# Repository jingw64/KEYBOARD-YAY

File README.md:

# J&R's Keyboard Project

## Overview

For this project, we wish to learn the process of making a keyboard. Due to how well documented and relatively simple keyboards are, we decided that creating one from the ground up will be a good first project for developing important skills.

After the completion of this project, we will:

- Understand the basics of navigating git and github
- Know the process of designing a PCB
- Develop collaboration skills
- Gain experience in writing software for an embedded system

## Projects Thus Far

- [~~Macropad~~ Burgerpad](./macropads/burgerpad/)
  - Our very first project in the keyboard series to get us familiar with software and the PCB designing process
  - A macropad in a layout that looks similar to a burger; made to print out Greek letters to make writing equations and lab reports easier

## Tools

### Softwares

- KiCad
  - For schematic and PCB design
- VSCode
  - For managing files on github and writing firmware
- Notion
  - For writing up documentation that require collaborative work
  
### Libraries

- [Marbastlib](https://github.com/ebastler/marbastlib?ref=ohmbedded.com)
  - A KiCad library specifically for designing keyboard PCBs

## References

### General Process

- [How to Build a Custom Keyboard From Scratch | Part 1 Layout and Design](https://www.youtube.com/watch?v=IJxuzyO9b8M) - Casual Coders
- [Custom Keyboard From Scratch Part 2](https://www.youtube.com/watch?v=fYNxG8RwpaE) - Casual Coders
- [How to Design Mechanical Keyboard PCBs with Kicad](https://www.youtube.com/watch?v=8WXpGTIbxlQ) - Joe Scotto

### Functionality

- [How a Mechanical Keyboard Works (Matrix and Direct Wiring)](https://www.youtube.com/watch?v=7LyziNdFlew) - Joe Scotto

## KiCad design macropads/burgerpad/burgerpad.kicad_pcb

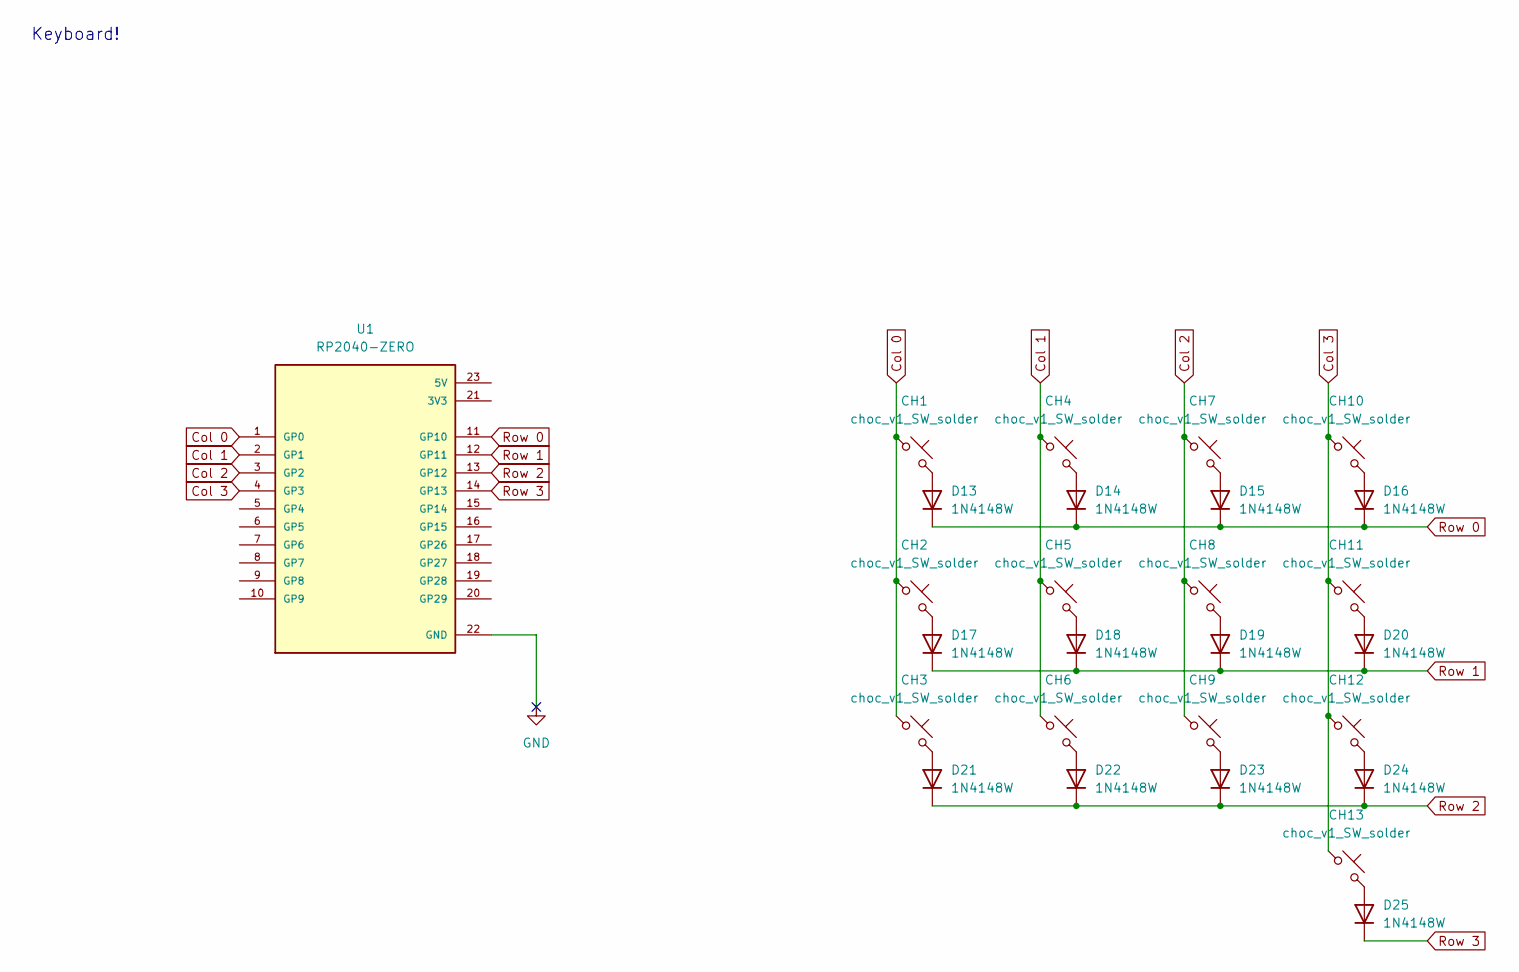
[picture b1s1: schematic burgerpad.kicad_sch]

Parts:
CH1, CH2, CH3, CH4, CH5, CH6, CH7, CH8, CH9, CH10, CH11, CH12, CH13: choc_v1_SW_solder; SW_choc_v1_1u
D13, D14, D15, D16, D17, D18, D19, D20, D21, D22, D23, D24, D25: 1N4148W; D_SOD-123
U1: RP2040-ZERO; MODULE_RP2040-ZERO; PARTREV NA

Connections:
Col 0: CH1.1, CH2.1, CH3.1, U1.1 (GP0)
Col 1: CH4.1, CH5.1, CH6.1, U1.2 (GP1)
Col 2: CH7.1, CH8.1, CH9.1, U1.3 (GP2)
Col 3: CH10.1, CH11.1, CH12.1, CH13.1, U1.4 (GP3)
GND: U1.22 (GND)
unnamed: CH1.2, D13.2 (A)
unnamed: CH4.2, D14.2 (A)
unnamed: CH7.2, D15.2 (A)
unnamed: CH10.2, D16.2 (A)
unnamed: CH2.2, D17.2 (A)
unnamed: CH5.2, D18.2 (A)
unnamed: CH8.2, D19.2 (A)
unnamed: CH11.2, D20.2 (A)
unnamed: CH3.2, D21.2 (A)
unnamed: CH6.2, D22.2 (A)
unnamed: CH9.2, D23.2 (A)
unnamed: CH12.2, D24.2 (A)
unnamed: CH13.2, D25.2 (A)
Row 0: D13.1 (K), D14.1 (K), D15.1 (K), D16.1 (K), U1.11 (GP10)
Row 1: D17.1 (K), D18.1 (K), D19.1 (K), D20.1 (K), U1.12 (GP11)
Row 2: D21.1 (K), D22.1 (K), D23.1 (K), D24.1 (K), U1.13 (GP12)
Row 3: D25.1 (K), U1.14 (GP13)

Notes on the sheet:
Keyboard!

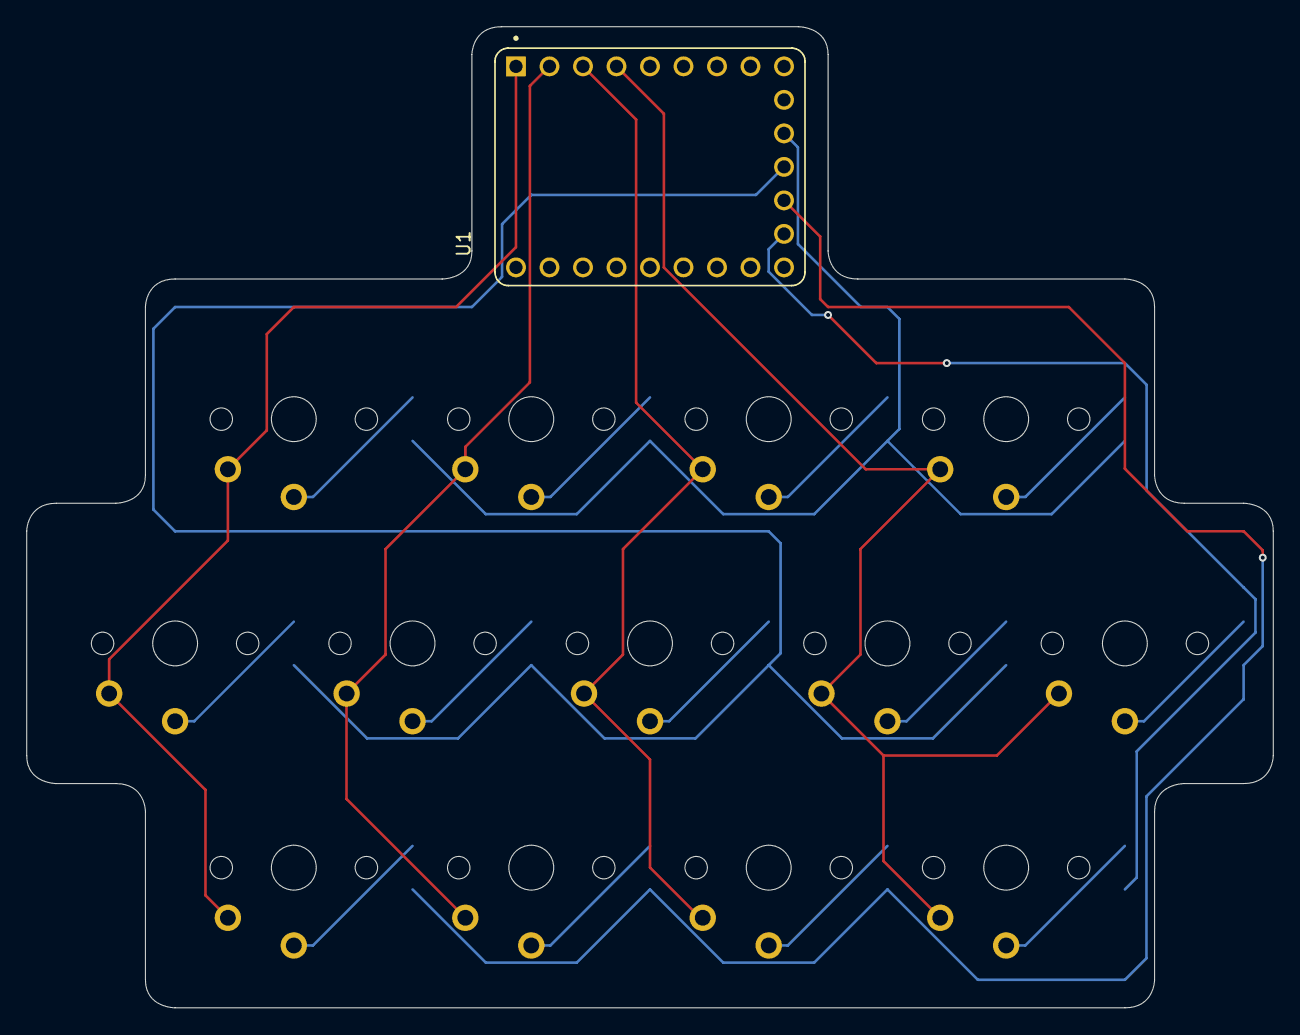
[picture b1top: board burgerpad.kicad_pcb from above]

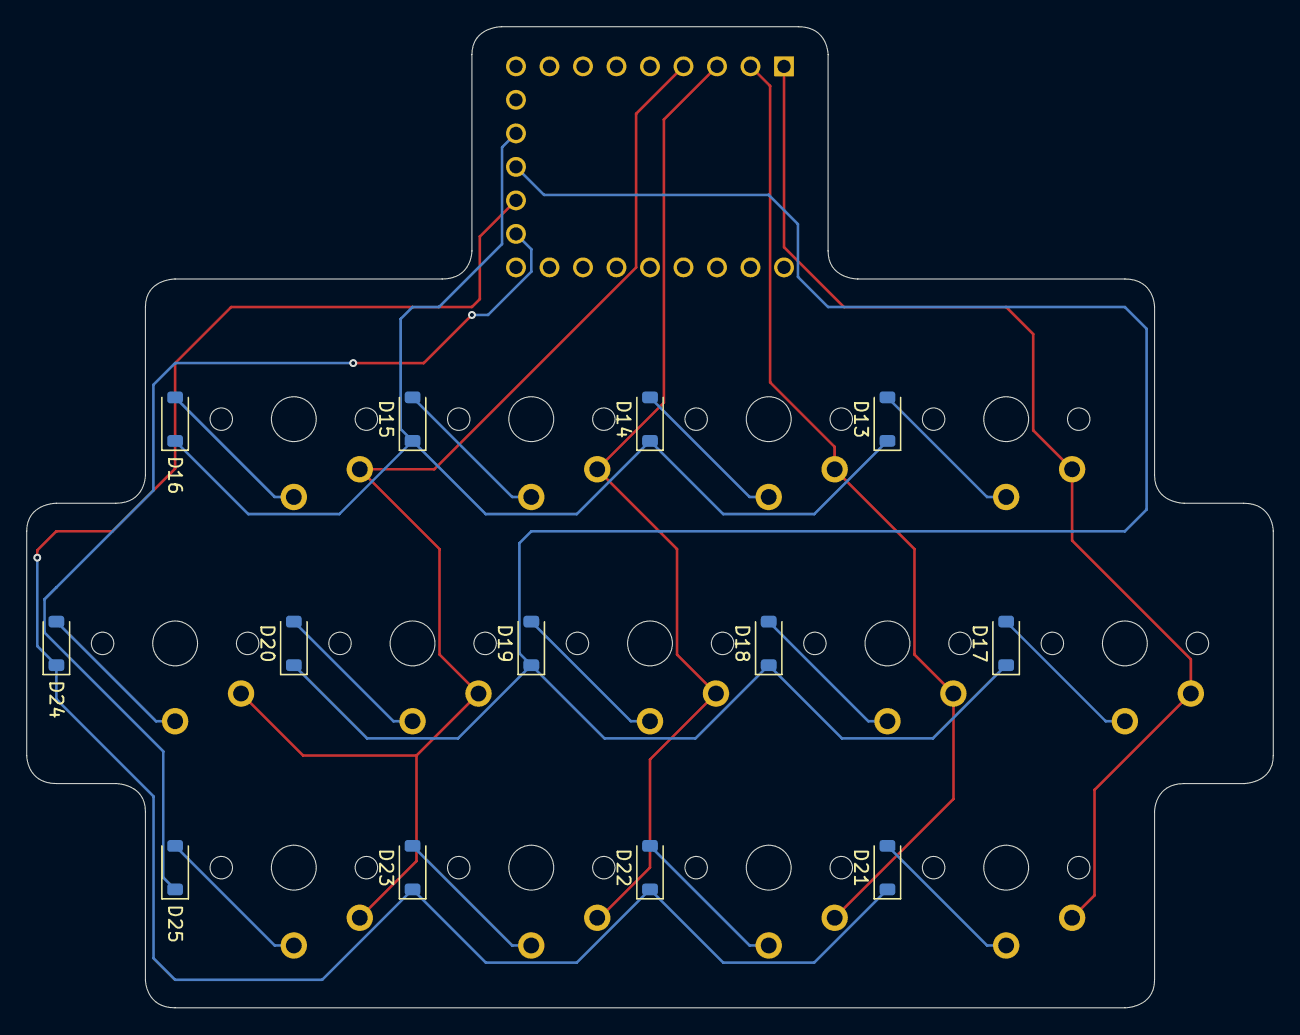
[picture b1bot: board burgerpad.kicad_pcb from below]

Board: 2 copper layers, 94.5 x 74.4 mm, 27 parts (13 on the bottom side), 21 nets.

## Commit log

2026-05-19 Added .gitignore
2026-05-20 skibidi rizz
2026-05-20 woah
2026-05-20 first project
2026-05-20 Added folder for macropad project
2026-05-20 moved macropad_v0 under macropad_proj
2026-05-20 removed dummy file
2026-05-20 Changed some docs
2026-05-20 Reorganized Macropad Log
2026-05-20 updated macropad log
2026-05-20 updated main readme
2026-05-20 updated main readme references
2026-05-20 changed formatting on macropad readme
2026-05-20 updated gitignore
2026-05-20 Created Microcontroller README
2026-05-21 uhh idk smth about like merging stuff
2026-05-21 linked macropad proj to main readme
2026-05-21 added firmware folder to macropad_proj
2026-05-21 Updated macropad name to burgerpad
2026-05-21 Added Keyboard Layout doc
2026-05-21 Updated some directory names and macropads_log
2026-05-21 Updated links in main readme
2026-05-21 Changed some file names
2026-05-21 Updated links in macropads_log readme
2026-05-21 Fixed formatting in readmes
2026-05-21 Updated Tools/Softwares section on main readme
2026-05-22 Added Switches + Keys to knowledge
2026-05-22 Made schematic and did PCB layouts
2026-05-22 Added an img to assets and updated macropads_log readme
2026-05-22 burgerpad borderpad
2026-05-22 updated macropad log with some images
2026-05-22 fixed a silly typo
2026-05-23 Added traces and ran DRC on PCB
2026-05-23 Updated macropads_log
2026-05-23 Updated burgerpad layout
2026-05-23 Updated schematic and PCB to match new layout
2026-05-23 Removed tools how-to and component selection under references section on main readme
2026-05-23 Updated macropad log and added knowledge
